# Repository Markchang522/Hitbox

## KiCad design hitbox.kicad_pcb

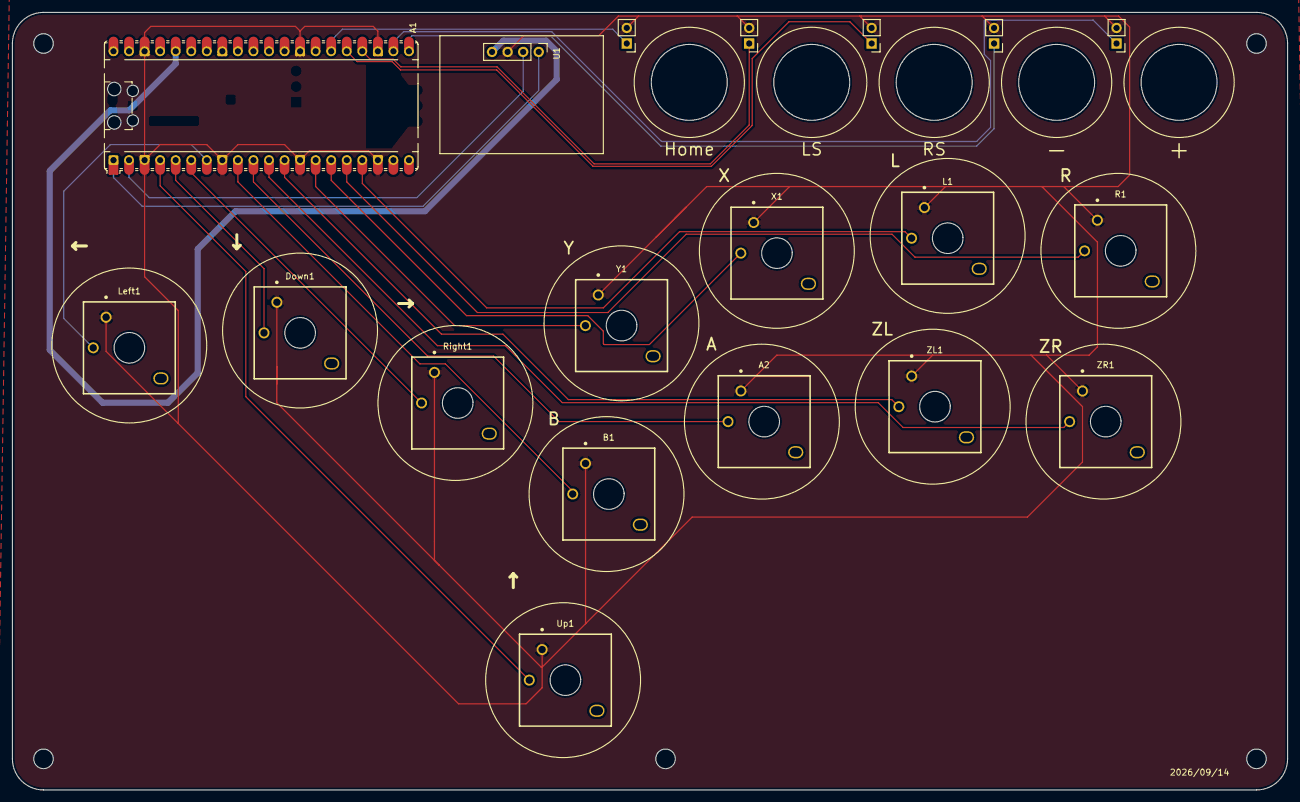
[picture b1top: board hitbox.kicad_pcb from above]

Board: 2 copper layers, 208.3 x 127.0 mm, 19 parts (0 on the bottom side), 21 nets.

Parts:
+: HBDGQ12B; PinHeader_1x02_P2.54mm_Vertical
-: HBDGQ12B; PinHeader_1x02_P2.54mm_Vertical
A1: RaspberryPi_Pico; RaspberryPi_Pico_Common_Unspecified
A2: cpg135301d02
B1: cpg135301d02
Down1: cpg135301d02
Home: HBDGQ12B; PinHeader_1x02_P2.54mm_Vertical
L1: cpg135301d02
LS: HBDGQ12B; PinHeader_1x02_P2.54mm_Vertical
Left1: cpg135301d02
R1: cpg135301d02
RS: HBDGQ12B; PinHeader_1x02_P2.54mm_Vertical
Right1: cpg135301d02
U1: ER_OLEDM0.91_1x-I2C; PinHeader_1x04_P2.54mm_Vertical
Up1: cpg135301d02
X1: cpg135301d02
Y1: cpg135301d02
ZL1: cpg135301d02
ZR1: cpg135301d02

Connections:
GND: +.2, -.2, A1.3 (GND), A1.8 (GND), A1.13 (GND), A1.18 (GND), A1.23 (GND), A1.28 (GND), A1.38 (GND), A2.1, B1.1, Down1.1, Home.2, L1.1, LS.2, Left1.1, R1.1, RS.2, Right1.1, U1.1 (GND), Up1.1, X1.1, Y1.1, ZL1.1, ZR1.1
unnamed: A1.36 (3V3), U1.2 (VCC)
unnamed: A1.1 (GPIO0), U1.4 (SDA)
unnamed: A1.2 (GPIO1), U1.3 (SCL)
unnamed: A1.4 (GPIO2), Up1.2
unnamed: A1.5 (GPIO3), Down1.2
unnamed: A1.6 (GPIO4), Right1.2
unnamed: A1.7 (GPIO5), Left1.2
unnamed: A1.9 (GPIO6), B1.2
unnamed: A1.10 (GPIO7), A2.2
unnamed: A1.11 (GPIO8), ZR1.2
unnamed: A1.12 (GPIO9), ZL1.2
unnamed: A1.14 (GPIO10), Y1.2
unnamed: A1.15 (GPIO11), X1.2
unnamed: A1.16 (GPIO12), R1.2
unnamed: A1.17 (GPIO13), L1.2
unnamed: -.1, A1.21 (GPIO16)
unnamed: +.1, A1.22 (GPIO17)
unnamed: A1.24 (GPIO18), LS.1
unnamed: A1.25 (GPIO19), RS.1
unnamed: A1.26 (GPIO20), Home.1
